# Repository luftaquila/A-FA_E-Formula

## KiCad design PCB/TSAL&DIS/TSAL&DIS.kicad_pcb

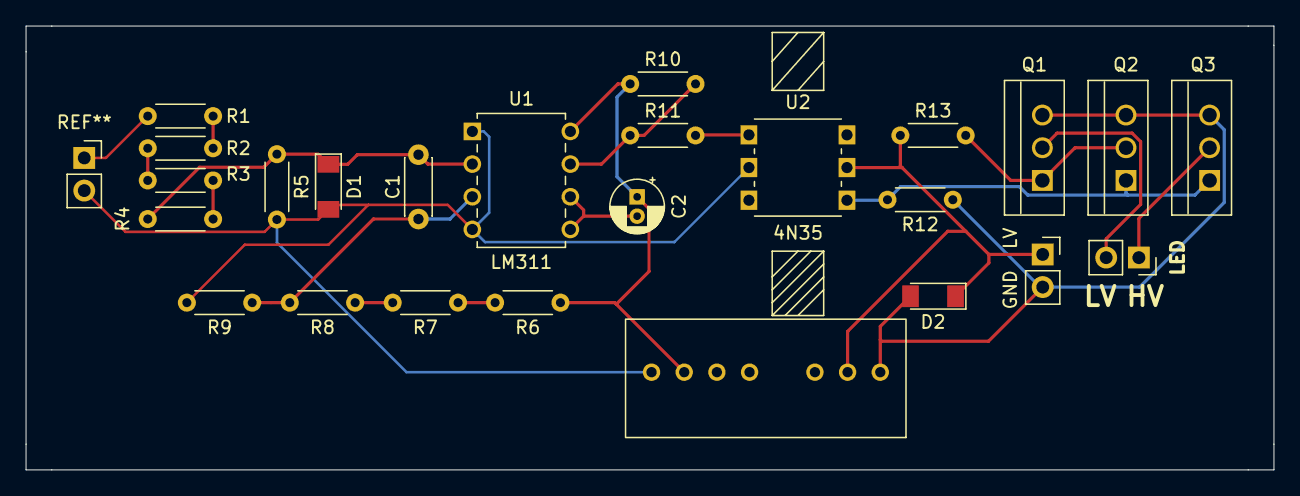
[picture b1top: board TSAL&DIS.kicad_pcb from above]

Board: 2 copper layers, 97.0 x 34.5 mm, 23 parts (0 on the bottom side), 16 nets.

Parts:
C1: 1nF; C_Disc_D4.3mm_W1.9mm_P5.00mm
C2: 1uF; CP_Radial_D4.0mm_P1.50mm
D1, D2: BZV55C12; D_MiniMELF
PS1: SPAN02A-12; SPAN02A-12[s.m]
Q1, Q2, Q3: IRF640; IRF640NPBF
R1, R2, R3, R4, R6, R7, R8, R9, R10: 4.7M; R_Axial_DIN0204_L3.6mm_D1.6mm_P5.08mm_Horizontal
R5: 1M; R_Axial_DIN0204_L3.6mm_D1.6mm_P5.08mm_Horizontal
R11: 2k2; R_Axial_DIN0204_L3.6mm_D1.6mm_P5.08mm_Horizontal
R12: 100k; R_Axial_DIN0204_L3.6mm_D1.6mm_P5.08mm_Horizontal
R13: 10k; R_Axial_DIN0204_L3.6mm_D1.6mm_P5.08mm_Horizontal
U1: LM311; LM311P
U2: 4N35

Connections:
/HV-: D1.2 (A), PS1.7 (-VOUT), R5.2, R9.2, U1.1 (GND), U1.4 (V-), U2.2
/LV: D2.1 (K), PS1.2 (+VIN), R13.1, U2.5
GND: D2.2 (A), PS1.1 (-VIN), Q1.3 (S), Q2.3 (S), Q3.3 (S), R12.1
unnamed: C1.1, R8.2, R9.1, U1.3 (-)
unnamed: C1.2, D1.1 (K), R4.2, R5.1, U1.2 (+)
unnamed: C2.1, PS1.6 (+VOUT), R6.1, R10.1, U1.8 (V+)
unnamed: C2.2, U1.5 (BAL), U1.6 (STRB)
unnamed: Q1.1 (G), Q2.2 (D), R13.2
unnamed: Q2.1 (G), Q3.1 (G), R12.2, U2.4
unnamed: R1.2, R2.1
unnamed: R2.2, R3.1
unnamed: R3.2, R4.1
unnamed: R6.2, R7.1
unnamed: R7.2, R8.1
unnamed: R10.2, R11.1, U1.7
unnamed: R11.2, U2.1

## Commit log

2022-05-04 REFACTOR
2022-05-04 UPDATE: gitignore
